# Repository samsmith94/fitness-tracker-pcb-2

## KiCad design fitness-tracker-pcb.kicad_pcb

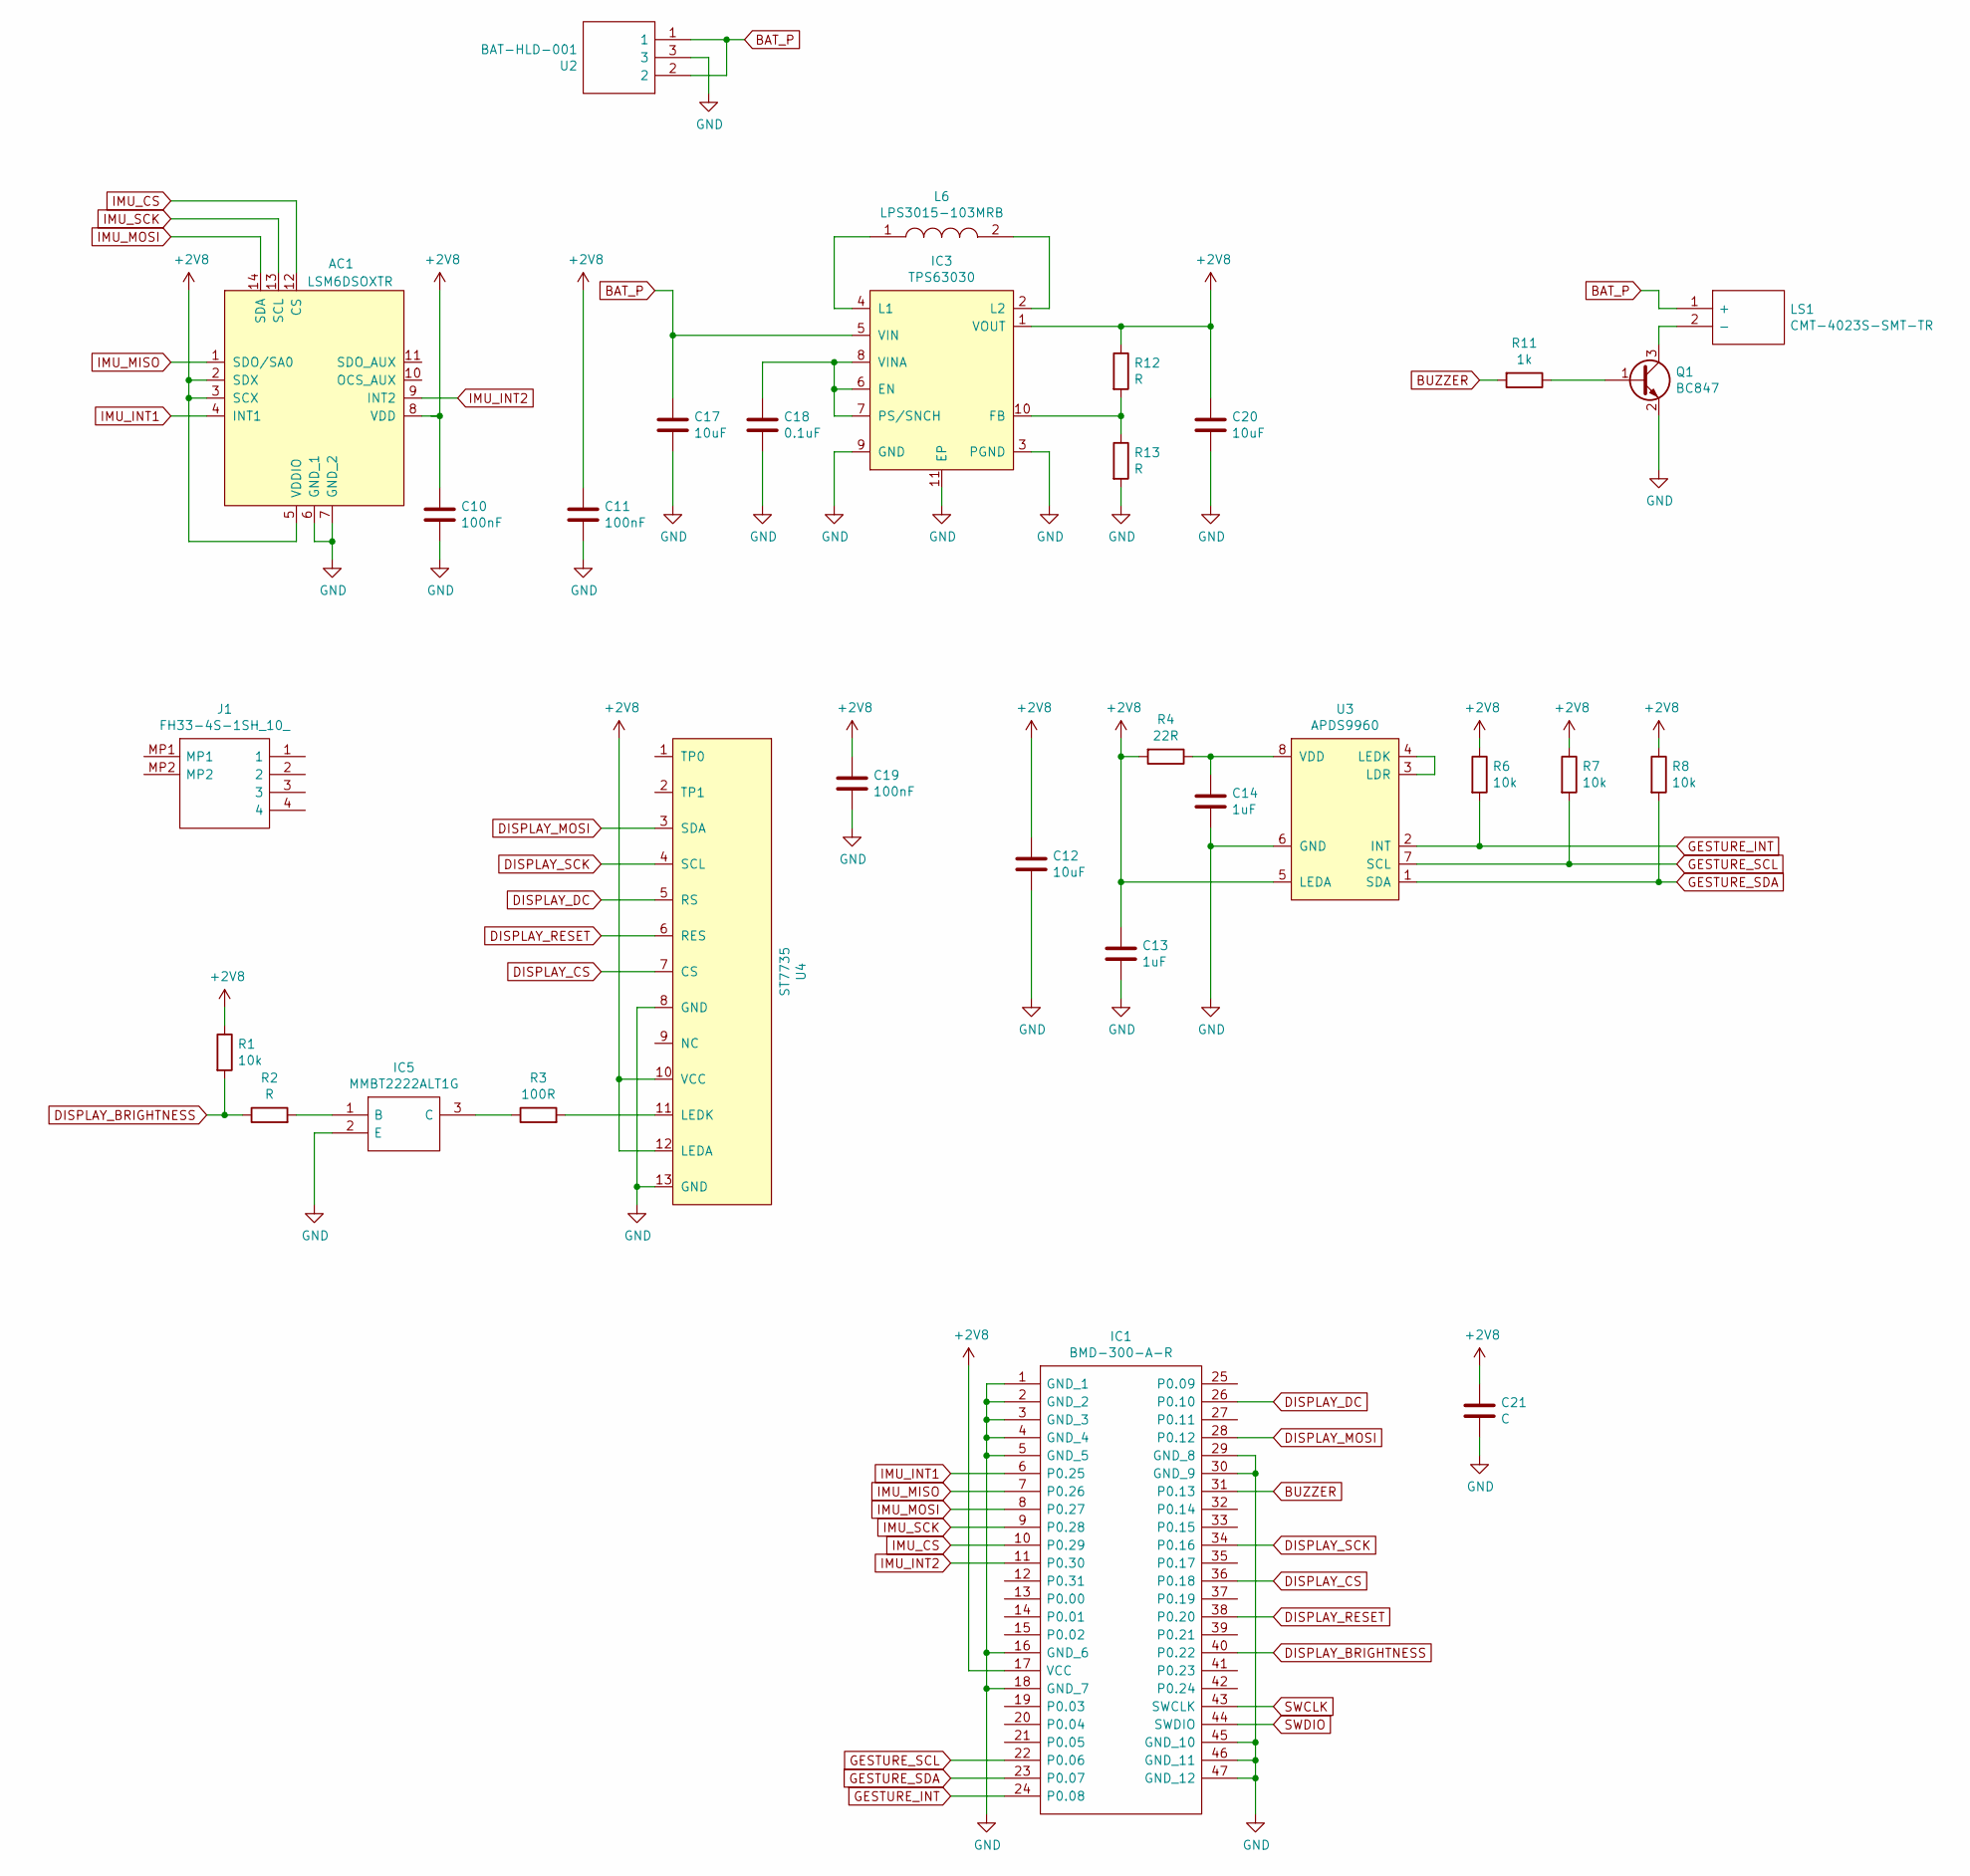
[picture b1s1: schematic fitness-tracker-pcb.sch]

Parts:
AC1: LSM6DSOXTR; LGA-14_1
C10, C11, C19: 100nF; C_0603_1608Metric
C12, C17, C20: 10uF; C_0603_1608Metric
C13, C14: 1uF; C_0603_1608Metric
C18: 0.1uF; C_0603_1608Metric
C21: C; C_0603_1608Metric
IC1: BMD-300-A-R; BMD300AR; Mouser Part Number 377-BMD300AR
IC3: TPS63030; SON50P250X250X80-11N-D
IC5: MMBT2222ALT1G; SOT96P237X111-3N; Mouser Part Number 863-MMBT2222ALT1G
J1: FH33-4S-1SH_10_; FH334S1SH10; Mouser Part Number 798-FH334S1SH10
L6: LPS3015-103MRB; LPS3015; Mouser Part Number 994-LPS3015-103MRB
LS1: CMT-4023S-SMT-TR; CMT-4023S; Mouser Part Number 490-CMT-4023S-SMT-TR
Q1: BC847; SOT-23
R1, R6, R7, R8: 10k; R_0603_1608Metric
R2, R12, R13: R; R_0603_1608Metric
R3: 100R; R_0603_1608Metric
R4: 22R; R_0603_1608Metric
R11: 1k; R_0603_1608Metric
U2: BAT-HLD-001; BATHLD001; Mouser Part Number 712-BAT-HLD-001
U3: APDS9960; APDS-9950
U4: ST7735; ST7735_curved

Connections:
+2V8: AC1.2 (SDX), AC1.3 (SCX), AC1.5 (VDDIO), AC1.8 (VDD), C10.1, C11.1, C12.1, C13.1, C19.1, C20.1, C21.1, IC1.17 (VCC), IC3.1 (VOUT), R1.1, R4.2, R6.1, R7.1, R8.1, R12.1, U3.5 (LEDA), U4.10 (VCC), U4.12 (LEDA)
BAT_P: C17.1, IC3.5 (VIN), LS1.1 (+), U2.1, U2.2
BUZZER: IC1.31 (P0.13), R11.2
DISPLAY_BRIGHTNESS: IC1.40 (P0.22), R1.2, R2.1
DISPLAY_CS: IC1.36 (P0.18), U4.7 (CS)
DISPLAY_DC: IC1.26 (P0.10), U4.5 (RS)
DISPLAY_MOSI: IC1.28 (P0.12), U4.3 (SDA)
DISPLAY_RESET: IC1.38 (P0.20), U4.6 (RES)
DISPLAY_SCK: IC1.34 (P0.16), U4.4 (SCL)
GESTURE_INT: IC1.24 (P0.08), R6.2, U3.2 (INT)
GESTURE_SCL: IC1.22 (P0.06), R7.2, U3.7 (SCL)
GESTURE_SDA: IC1.23 (P0.07), R8.2, U3.1 (SDA)
GND: AC1.6 (GND_1), AC1.7 (GND_2), C10.2, C11.2, C12.2, C13.2, C14.2, C17.2, C18.2, C19.2, C20.2, C21.2, IC1.1 (GND_1), IC1.2 (GND_2), IC1.3 (GND_3), IC1.4 (GND_4), IC1.5 (GND_5), IC1.16 (GND_6), IC1.18 (GND_7), IC1.29 (GND_8), IC1.30 (GND_9), IC1.45 (GND_10), IC1.46 (GND_11), IC1.47 (GND_12), IC3.3 (PGND), IC3.9 (GND), IC3.11 (EP), IC5.2 (E), Q1.2 (E), R13.2, U2.3, U3.6 (GND), U4.8 (GND), U4.13 (GND)
IMU_CS: AC1.12 (CS), IC1.10 (P0.29)
IMU_INT1: AC1.4 (INT1), IC1.6 (P0.25)
IMU_INT2: AC1.9 (INT2), IC1.11 (P0.30)
IMU_MISO: AC1.1 (SDO/SA0), IC1.7 (P0.26)
IMU_MOSI: AC1.14 (SDA), IC1.8 (P0.27)
IMU_SCK: AC1.13 (SCL), IC1.9 (P0.28)
unnamed: C14.1, R4.1, U3.8 (VDD)
unnamed: C18.1, IC3.6 (EN), IC3.7 (PS/SNCH), IC3.8 (VINA)
unnamed: IC3.2 (L2), L6.2
unnamed: IC3.4 (L1), L6.1
unnamed: IC3.10 (FB), R12.2, R13.1
unnamed: IC5.1 (B), R2.2
unnamed: IC5.3 (C), R3.1
unnamed: LS1.2 (-), Q1.3 (C)
unnamed: Q1.1 (B), R11.1
unnamed: R3.2, U4.11 (LEDK)
unnamed: U3.3 (LDR), U3.4 (LEDK)
SWCLK: IC1.43 (SWCLK)
SWDIO: IC1.44 (SWDIO)

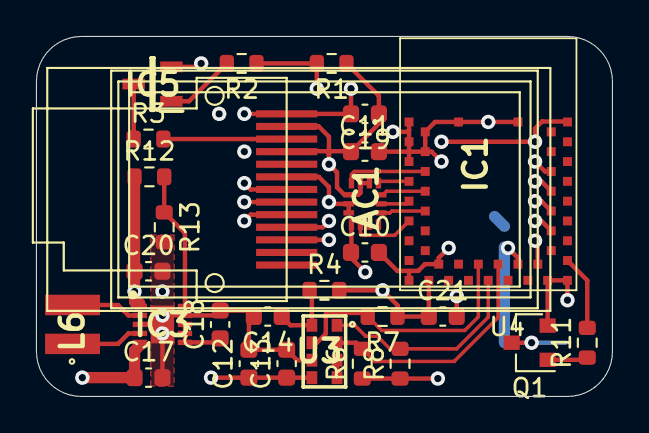
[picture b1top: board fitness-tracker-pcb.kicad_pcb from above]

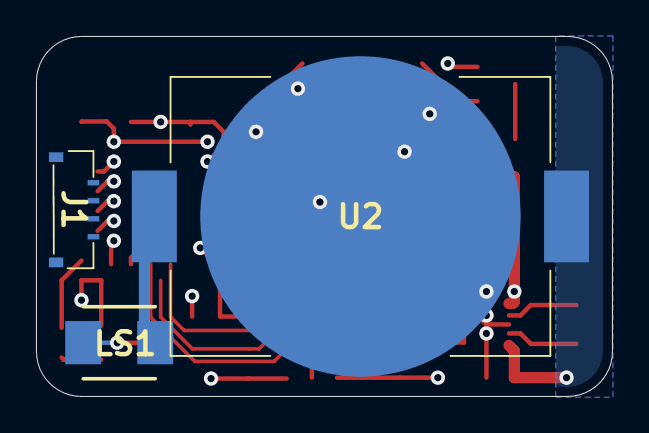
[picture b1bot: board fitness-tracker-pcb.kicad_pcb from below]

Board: 4 copper layers, 32.0 x 20.0 mm, 31 parts (3 on the bottom side), 30 nets.

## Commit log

2020-12-19 init repo
2020-12-20 amost done arrange
2020-12-21 add 2 inner layer
2020-12-21 add some wiring
2020-12-24 before remove unnecessary parts
2020-12-24 almost done 4 layer pcb
2020-12-24 done? drv good!
